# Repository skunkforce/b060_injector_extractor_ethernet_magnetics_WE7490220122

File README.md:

# edgy_board number b060
This design is part of the [edgy board project](https://github.com/skunkforce/edgy_boards). It provides a >1A raited gigabit capable ethernet transformer with center taps exposed on both sides. This can be used for PoE extractor or injector circuits. 

# getting started
This repository uses submodules. After cloning use the command 

```$ git submodule update --init --recursive```

to pull the submodules before opening the project with kicad. 

# Tests
Tests can be found in [TESTS.md](TESTS.md)

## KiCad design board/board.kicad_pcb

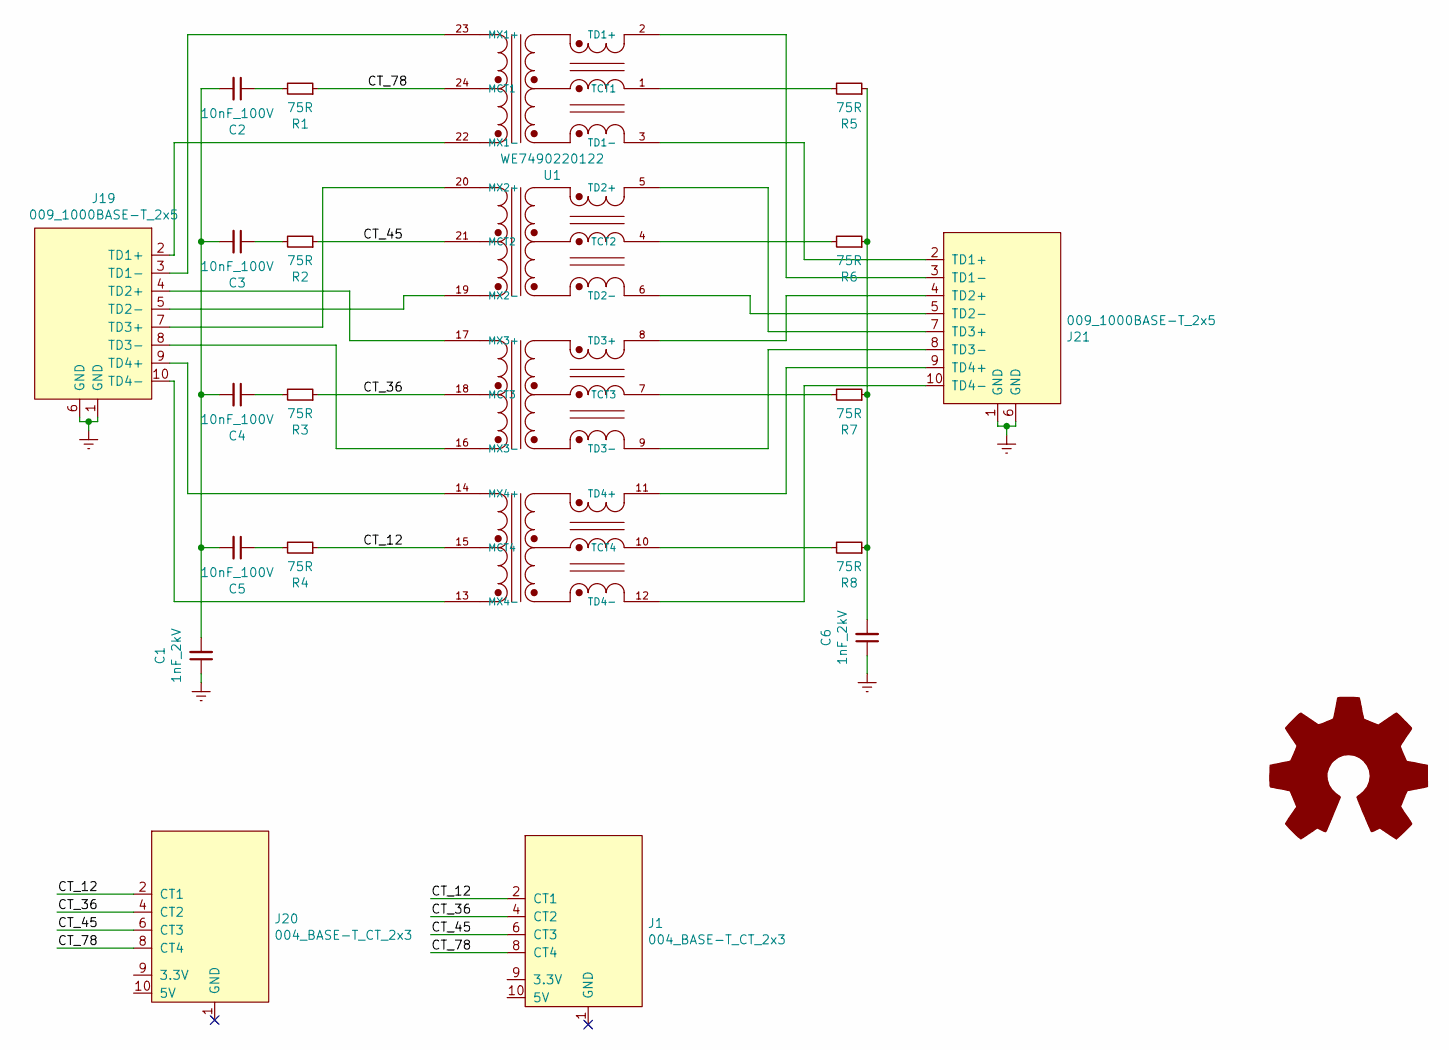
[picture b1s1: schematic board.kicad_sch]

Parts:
C1, C6: 1nF_2kV; C_1210_3225Metric; Voltage 2000; MPN CL32B102KJFNNNE
C2, C3, C4, C5: 10nF_100V; C_0603_1608Metric; Voltage 100; MPN ‎CL10B103KC8NNNC‎
J1: 004_BASE-T_CT_2x3; on_edge_2x05_device
J19, J21: 009_1000BASE-T_2x5; on_edge_2x05_host
J20: 004_BASE-T_CT_2x3; on_edge_2x05_host
R1, R2, R3, R4, R5, R6, R7, R8: 75R; R_0805_2012Metric; MPN ‎RMCF0805FT75R0‎
U1: WE7490220122; XFMR_7490220122; MPN 7490220122; Digi-Key_PN 732-10731-1-ND
l1: Logo_Open_Hardware_Large; OSHW-Logo2_7.3x6mm_SilkScreen

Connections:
/CT_12: J1.2 (CT1), J20.2 (CT1), R4.1, U1.15 (MCT4)
/CT_36: J1.4 (CT2), J20.4 (CT2), R3.1, U1.18 (MCT3)
/CT_45: J1.6 (CT3), J20.6 (CT3), R2.1, U1.21 (MCT2)
/CT_78: J1.8 (CT4), J20.8 (CT4), R1.1, U1.24 (MCT1)
Earth: C1.1, C6.1, J19.1 (GND), J19.6 (GND), J21.1 (GND), J21.6 (GND)
unnamed: C1.2, C2.2, C3.2, C4.2, C5.2
unnamed: C2.1, R1.2
unnamed: C3.1, R2.2
unnamed: C4.1, R3.2
unnamed: C5.1, R4.2
unnamed: C6.2, R5.1, R6.1, R7.1, R8.1
unnamed: J19.2 (TD1+), U1.22 (MX1-)
unnamed: J19.3 (TD1-), U1.23 (MX1+)
unnamed: J19.4 (TD2+), U1.17 (MX3+)
unnamed: J19.5 (TD2-), U1.19 (MX2-)
unnamed: J19.7 (TD3+), U1.20 (MX2+)
unnamed: J19.8 (TD3-), U1.16 (MX3-)
unnamed: J19.9 (TD4+), U1.14 (MX4+)
unnamed: J19.10 (TD4-), U1.13 (MX4-)
unnamed: J21.2 (TD1+), U1.3 (TD1-)
unnamed: J21.3 (TD1-), U1.2 (TD1+)
unnamed: J21.4 (TD2+), U1.8 (TD3+)
unnamed: J21.5 (TD2-), U1.6 (TD2-)
unnamed: J21.7 (TD3+), U1.5 (TD2+)
unnamed: J21.8 (TD3-), U1.9 (TD3-)
unnamed: J21.9 (TD4+), U1.11 (TD4+)
unnamed: J21.10 (TD4-), U1.12 (TD4-)
unnamed: R5.2, U1.1 (TCT1)
unnamed: R6.2, U1.4 (TCT2)
unnamed: R7.2, U1.7 (TCT3)
unnamed: R8.2, U1.10 (TCT4)

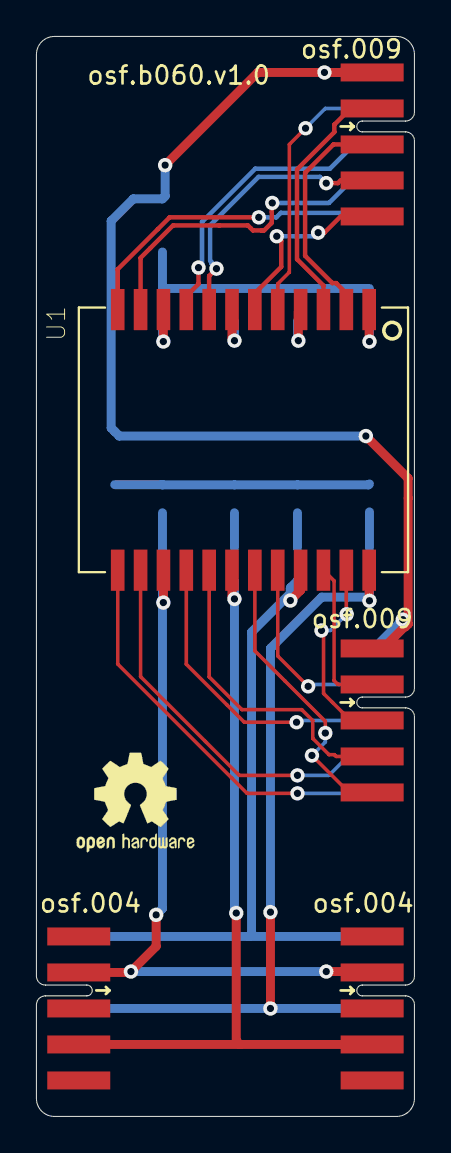
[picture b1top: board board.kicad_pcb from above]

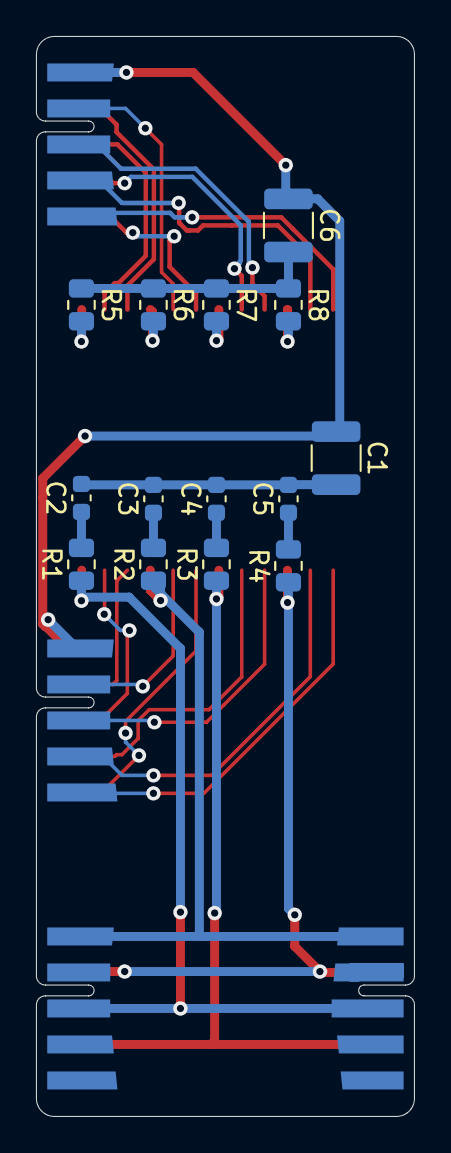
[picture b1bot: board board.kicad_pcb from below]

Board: 2 copper layers, 21.0 x 60.0 mm, 20 parts (14 on the bottom side), 31 nets.

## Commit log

2023-02-24 improved description
2023-02-24 imported legacy version
2023-05-14 refactored to use modern connectors and layout
